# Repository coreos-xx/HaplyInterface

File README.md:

# Introduction
This a PCB interface board for the Haply Haptic Device https://www.haply.co/ 
The PCB features an ESP32 WROOM wifi and Bluetooth MCU, a BNO055 IMU, battery charging with load sharing, and a USB2 type C connector for programming the controller.
It has 4 GPIO outputs of which 2 can be used as analog inputs as well.
# Use
Just clone the project, open the "Haply_EE.kicad_pro" with KiCAD 7.x, and enjoy. 
For production use the files in the "production" folder. 

# Pictures

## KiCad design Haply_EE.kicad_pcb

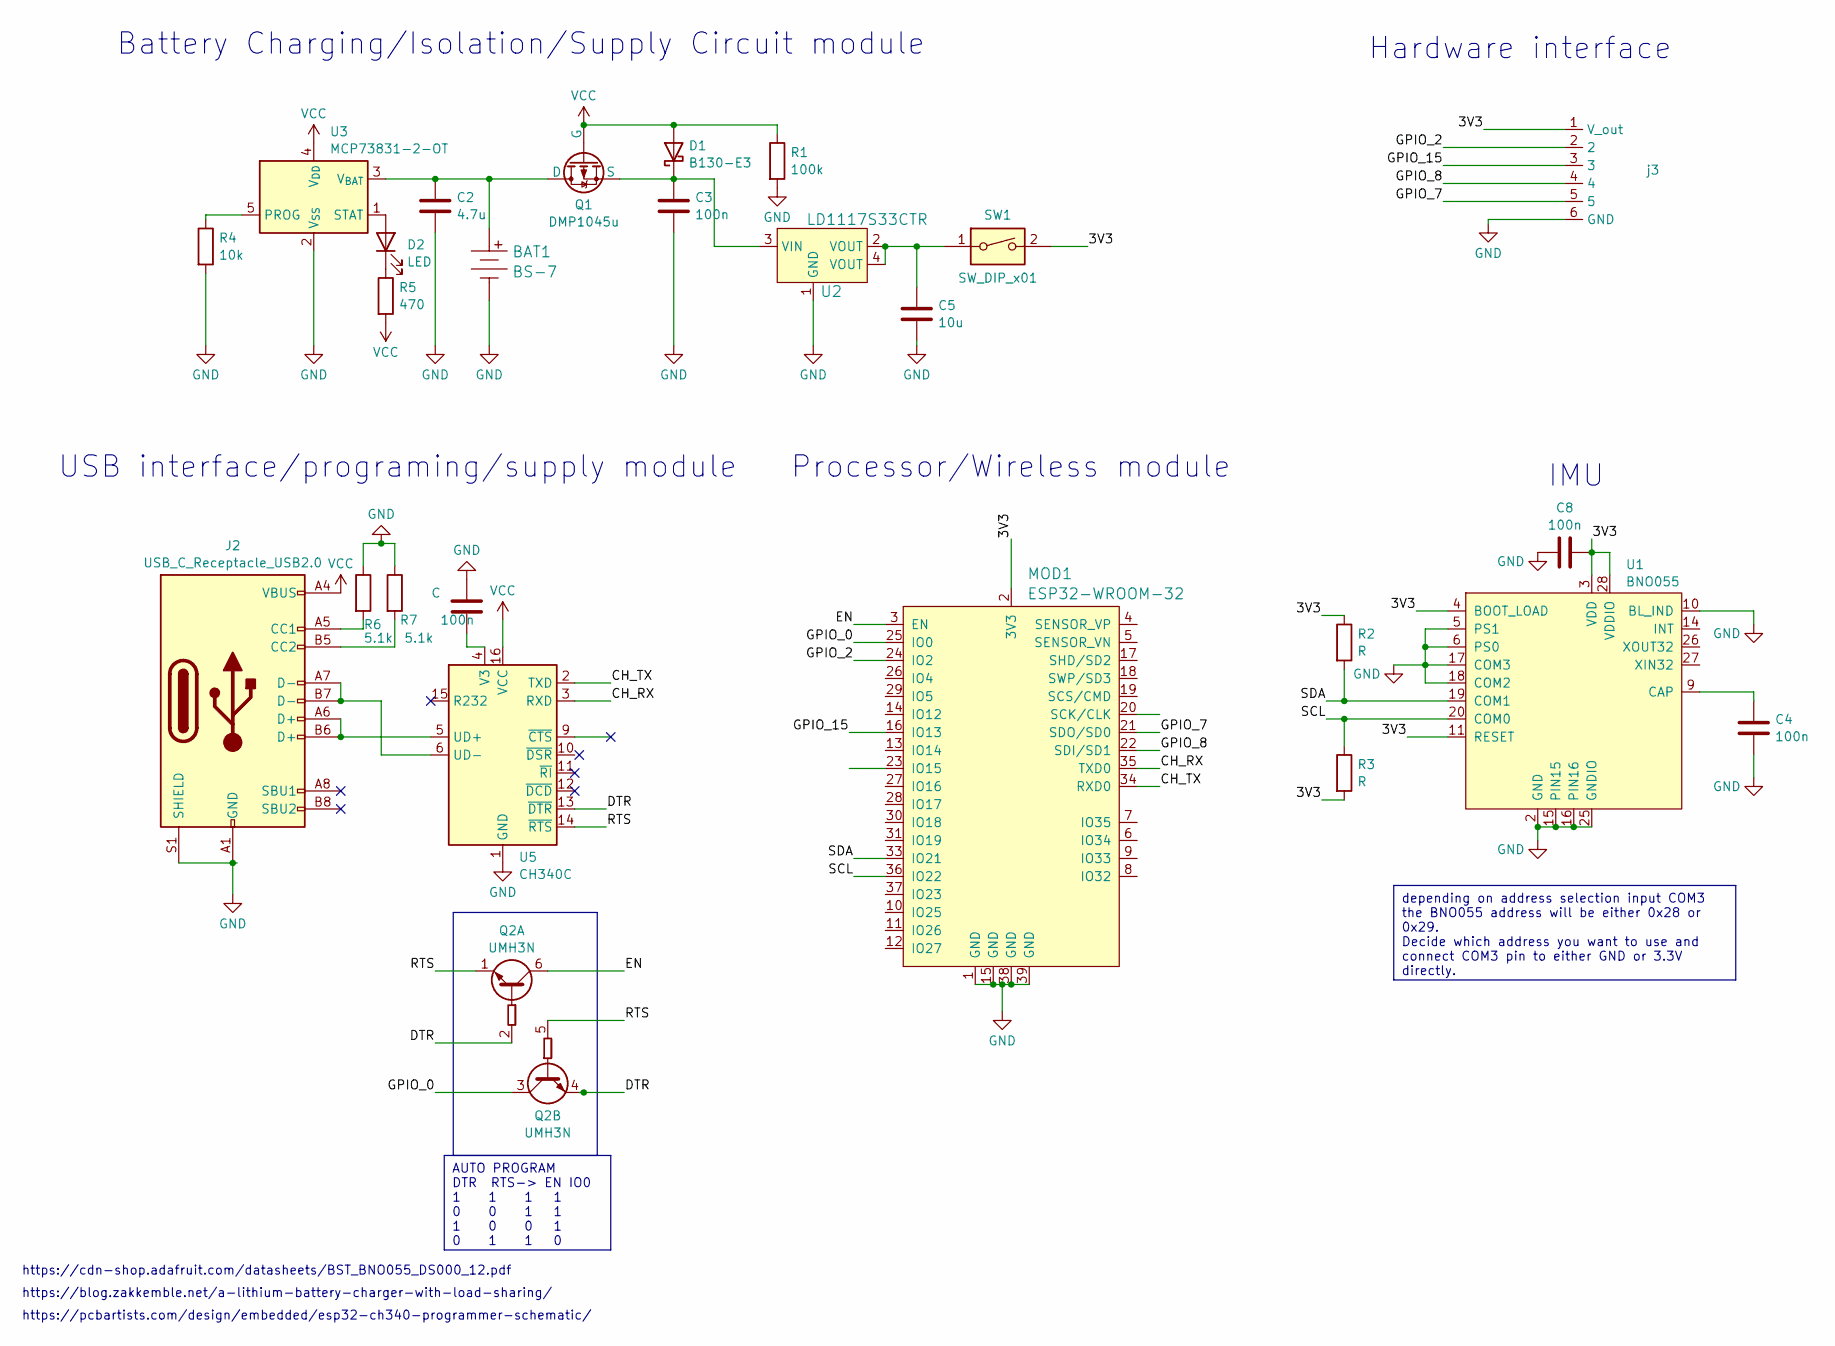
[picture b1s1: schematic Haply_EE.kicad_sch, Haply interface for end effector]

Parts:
BAT1: BS-7; batPads; MPN BS-7; Digi-Key_PN BS-7-ND
C, C3, C4, C8: 100n; C_0603_1608Metric
C2: 4.7u; C_0603_1608Metric
C5: 10u; C_0603_1608Metric
D1: B130-E3; D_SMA
D2: LED; LED_0603_1608Metric
J2: USB_C_Receptacle_USB2.0; USB_C_Receptacle_GCT_USB4110
MOD1: ESP32-WROOM-32; ESP32-WROOM-32D; MPN ESP32-WROOM-32; Digi-Key_PN 1904-1010-1-ND
Q1: DMP1045u; SOT-23-3
Q2: UMH3N; SOT-363_SC-70-6
R1: 100k; R_0603_1608Metric
R2, R3: R; R_0603_1608Metric
R4: 10k; R_0603_1608Metric
R5: 470; R_0603_1608Metric
R6, R7: 5.1k; R_0603_1608Metric
SW1: SW_DIP_x01; SW_SPDT_PCM12
U1: BNO055; LGA-28_5.2x3.8mm_BNO0055; MPN BNO055; Digi-Key_PN 828-1058-1-ND
U2: LD1117S33CTR; SOT-223; MPN LD1117S33CTR; Digi-Key_PN 497-1241-1-ND
U3: MCP73831-2-OT; SOT-23-5
U5: CH340C; SOIC-16_3.9x9.9mm_P1.27mm
j3: connectorHaply

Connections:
/3V3: C8.2, MOD1.2 (3V3), R2.1, R3.2, SW1.2, U1.3 (VDD), U1.4 (BOOT_LOAD), U1.11 (RESET), U1.28 (VDDIO), j3.1 (V_out)
/CH_RX: MOD1.35 (TXD0), U5.3 (RXD)
/CH_TX: MOD1.34 (RXD0), U5.2 (TXD)
/DTR: Q2.2 (B1), Q2.4 (E2), U5.13 (~DTR)
/EN: MOD1.3 (EN), Q2.6 (C1)
/GPIO_0: MOD1.25 (IO0), Q2.3 (C2)
/GPIO_2: MOD1.24 (IO2), j3.2
/GPIO_7: MOD1.21 (SDO/SD0), j3.5
/GPIO_8: MOD1.22 (SDI/SD1), j3.4
/GPIO_15: MOD1.16 (IO13), j3.3
/RTS: Q2.1 (E1), Q2.5 (B2), U5.14 (~RTS)
/SCL: MOD1.36 (IO22), R3.1, U1.20 (COM0)
/SDA: MOD1.33 (IO21), R2.2, U1.19 (COM1)
GND: BAT1.Neg, C.1, C2.2, C3.2, C4.2, C5.2, C8.1, J2.A1 (GND), J2.A12 (GND), J2.B1 (GND), J2.B12 (GND), J2.S1 (SHIELD), MOD1.1 (GND), MOD1.15 (GND), MOD1.38 (GND), MOD1.39 (GND), R1.2, R4.2, R6.1, R7.1, U1.2 (GND), U1.5 (PS1), U1.6 (PS0), U1.10 (BL_IND), U1.15 (PIN15), U1.16 (PIN16), U1.17 (COM3), U1.18 (COM2), U1.25 (GNDIO), U2.1 (GND), U3.2 (V_{SS}), U5.1 (GND), j3.6 (GND); also elsewhere on the board
unnamed: C5.1, SW1.1, U2.2 (VOUT), U2.4 (VOUT)
unnamed: C3.1, D1.1 (K), Q1.3 (S), U2.3 (VIN)
unnamed: D2.2 (A), U3.1 (STAT)
unnamed: D2.1 (K), R5.1
unnamed: J2.A5 (CC1), R6.2
unnamed: J2.B5 (CC2), R7.2
unnamed: BAT1.Pos, C2.1, Q1.1 (D), U3.3 (V_{BAT})
unnamed: C4.1, U1.9 (CAP)
unnamed: R4.1, U3.5 (PROG)
unnamed: J2.A6 (D+), J2.B6 (D+), U5.5 (UD+)
unnamed: J2.A7 (D-), J2.B7 (D-), U5.6 (UD-)
unnamed 25: C.2, U5.4 (V3); also elsewhere on the board
VCC: D1.2 (A), J2.A4 (VBUS), J2.A9 (VBUS), J2.B4 (VBUS), J2.B9 (VBUS), Q1.2 (G), R1.1, R5.2, U3.4 (V_{DD}), U5.16 (VCC)

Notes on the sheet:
AUTO PROGRAM DTR RTS-> EN IO0 1 1 1 1 0 0 1 1 1 0 0 1 0 1 1 0
depending on address selection input COM3 the BNO055 address will be either 0x28 or 0x29. Decide which address you want to use and connect COM3 pin to either GND or 3.3V directly.
Battery Charging/Isolation/Supply Circuit module
USB interface/programing/supply module
Processor/Wireless module
IMU
https://pcbartists.com/design/embedded/esp32-ch340-programmer-schematic/
https://blog.zakkemble.net/a-lithium-battery-charger-with-load-sharing/
Hardware interface
https://cdn-shop.adafruit.com/datasheets/BST_BNO055_DS000_12.pdf

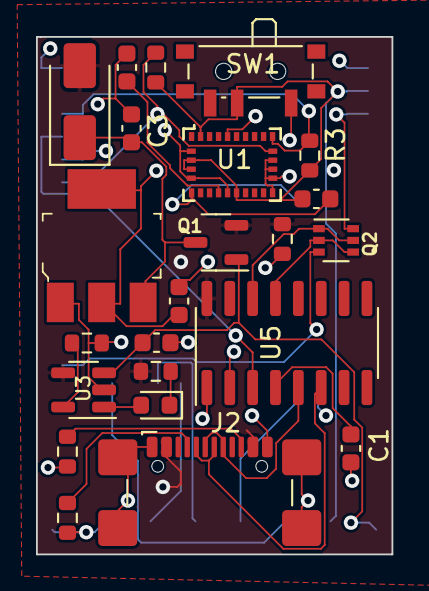
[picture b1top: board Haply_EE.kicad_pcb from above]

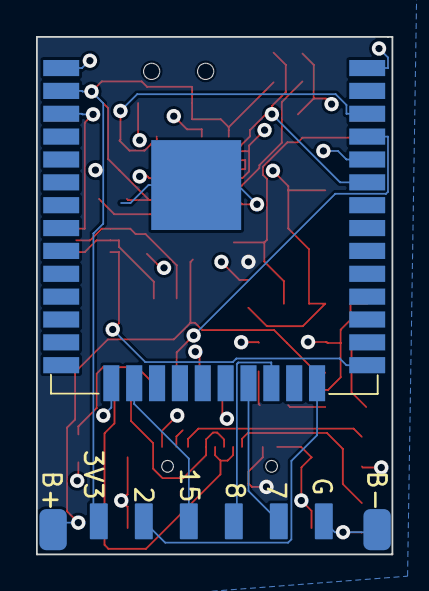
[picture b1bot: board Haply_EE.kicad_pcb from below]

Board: 4 copper layers, 19.8 x 28.8 mm, 26 parts (3 on the bottom side), 27 nets.

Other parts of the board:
C1: 100n; C_0603_1608Metric

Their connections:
GND: C1.1; also elsewhere on the board
unnamed 25: C1.2; also elsewhere on the board

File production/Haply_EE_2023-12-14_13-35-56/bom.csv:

Designator,Footprint,Quantity,Value,LCSC Part #
BAT1,batPads,1,BS-7,BS-7
"C1, C3, C4, C8",0603,4,100n,
C2,0603,1,4.7u,
C5,0603,1,10u,
D1,D_SMA,1,B130-E3,
D2,0603,1,LED,
J2,USB_C_Receptacle_GCT_USB4110,1,USB_C_Receptacle_USB2.0,
MOD1,ESP32-WROOM-32D,1,ESP32-WROOM-32,ESP32-WROOM-32
Q1,SOT-23-3,1,DMP1045u,
Q2,SOT-363_SC-70-6,1,UMH3N,
R1,0603,1,100k,
"R2, R3",0603,2,R,
R4,0603,1,10k,
R5,0603,1,470,
"R6, R7",0603,2,5.1k,
SW1,SW_SPDT_PCM12,1,SW_DIP_x01,
U1,LGA-28_5.2x3.8mm_BNO0055,1,BNO055,BNO055
U2,SOT-223,1,LD1117S33CTR,LD1117S33CTR
U3,SOT-23-5,1,MCP73831-2-OT,
U5,SOIC-16_3.9x9.9mm_P1.27mm,1,CH340C,
j3,connectorHaply,1,~,

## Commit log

2023-12-20 A first commit
2025-03-18 Added .gitignore
2025-03-18 removed tracked files now in .gitignore
